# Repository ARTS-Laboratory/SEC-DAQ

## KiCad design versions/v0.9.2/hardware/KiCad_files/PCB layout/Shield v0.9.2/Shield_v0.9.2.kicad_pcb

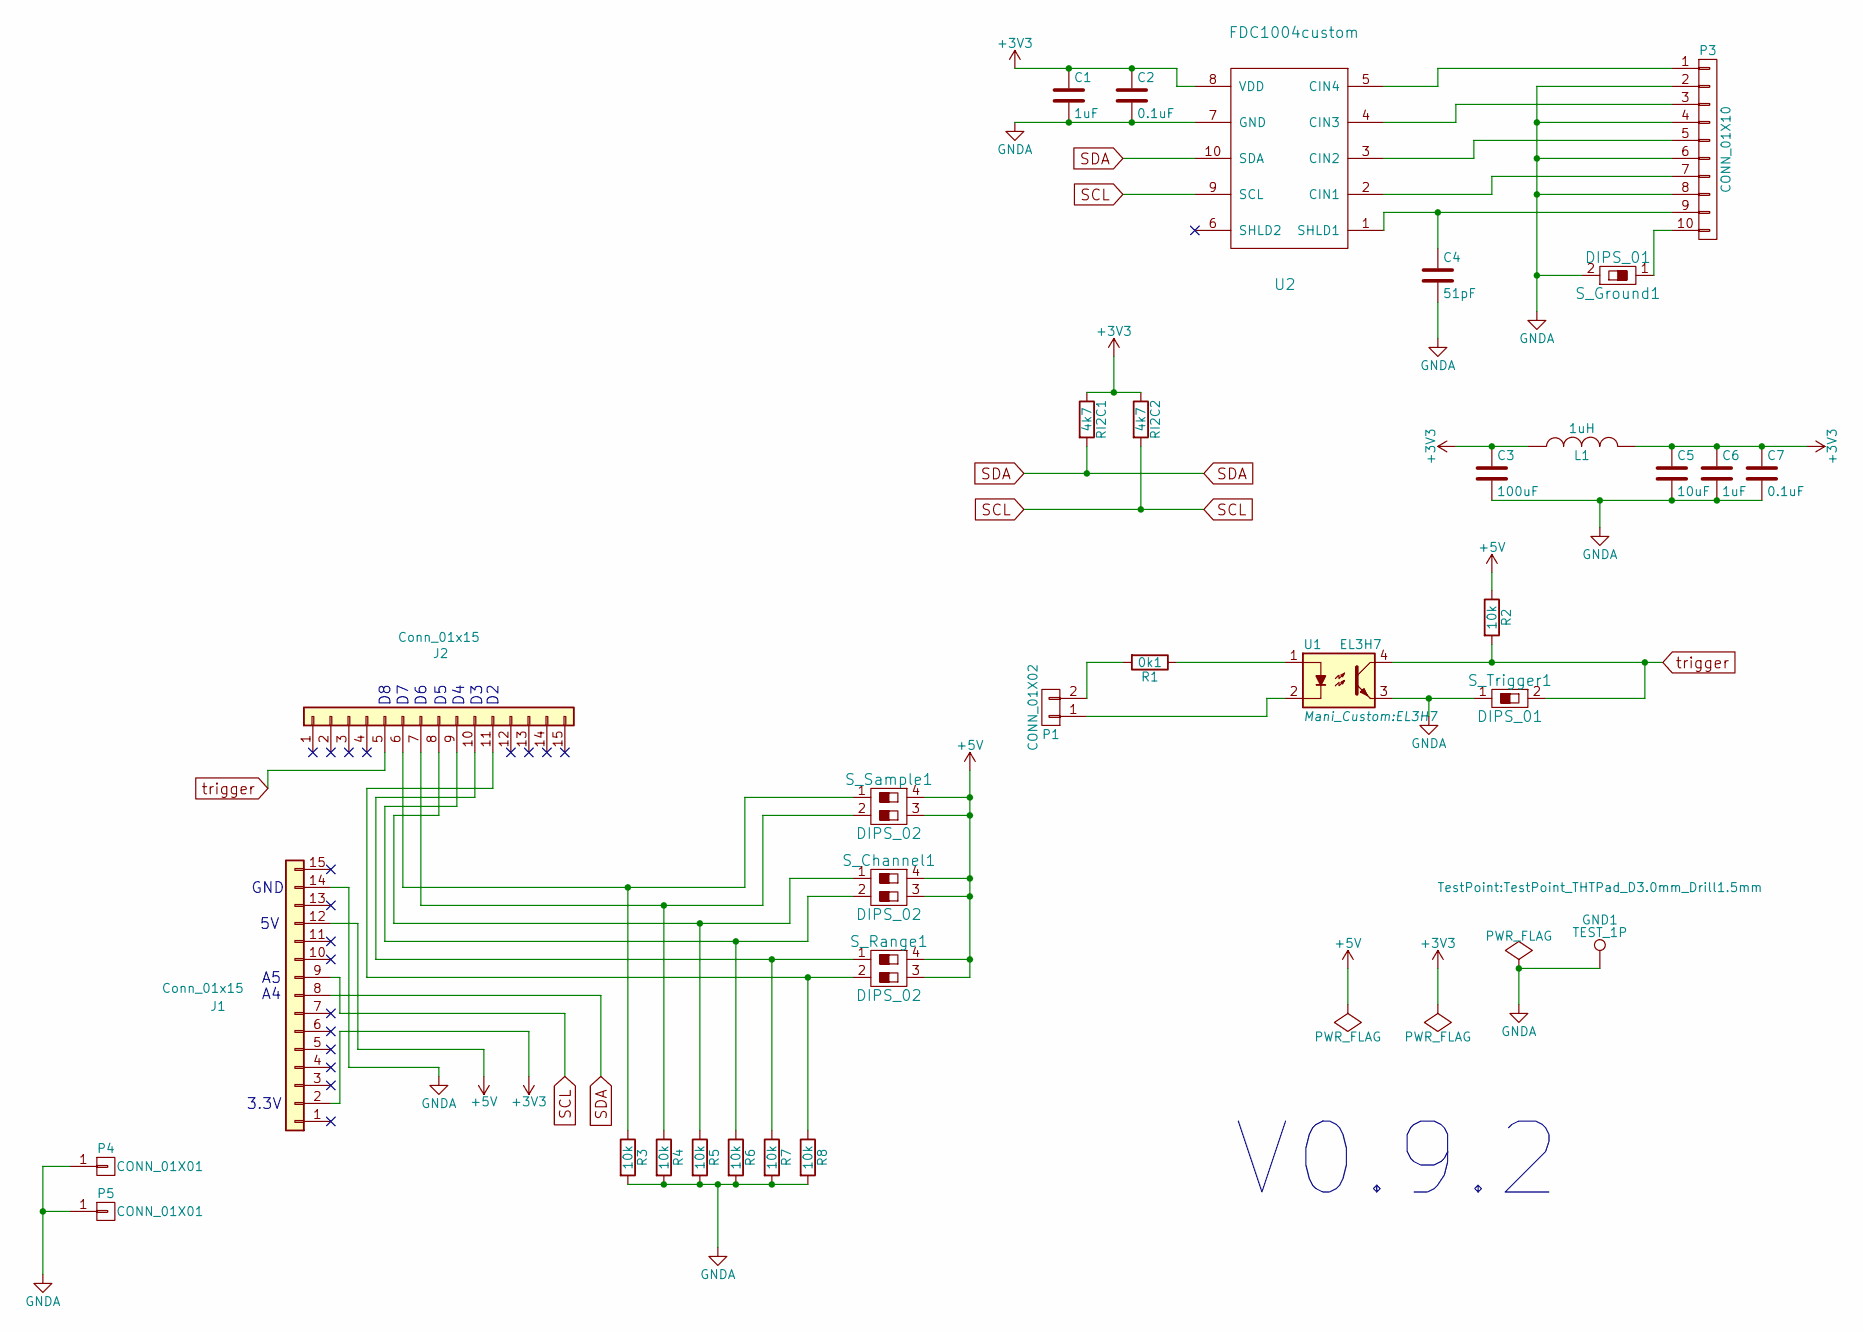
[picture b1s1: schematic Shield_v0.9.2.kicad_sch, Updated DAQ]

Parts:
C1, C6: 1uF; C_0805_2012Metric_Pad1.18x1.45mm_HandSolder
C2, C7: 0.1uF; C_0805_2012Metric_Pad1.18x1.45mm_HandSolder
C3: 100uF; C_1206_3216Metric_Pad1.33x1.80mm_HandSolder
C4: 51pF; C_0805_2012Metric_Pad1.18x1.45mm_HandSolder
C5: 10uF; C_0805_2012Metric_Pad1.18x1.45mm_HandSolder
GND1: TEST_1P; TestPoint_THTPad_D3.0mm_Drill1.5mm
J1, J2: Conn_01x15; PinSocket_1x15_P2.54mm_Vertical
L1: 1uH; R_0805_2012Metric_Pad1.20x1.40mm_HandSolder
P1: CONN_01X02; PinHeader_1x02_P2.54mm_Vertical
P3: CONN_01X10; DSUB-9_surface_mount
P4, P5: CONN_01X01; GNDA_Pad_4.064mm
R1: 0k1; R_1206_3216Metric_Pad1.30x1.75mm_HandSolder
R2, R3, R4, R5, R6, R7, R8: 10k; R_1206_3216Metric_Pad1.30x1.75mm_HandSolder
RI2C1, RI2C2: 4k7; R_1206_3216Metric_Pad1.30x1.75mm_HandSolder
S_Channel1: DIPS_02; SW_DIP_SPSTx02_Slide_9.78x7.26mm_W7.62mm_P2.54mm
S_Ground1: DIPS_01; SW_DIP_SPSTx01_Slide_9.78x4.72mm_W7.62mm_P2.54mm
S_Range1: DIPS_02; SW_DIP_SPSTx02_Slide_9.78x7.26mm_W7.62mm_P2.54mm
S_Sample1: DIPS_02; SW_DIP_SPSTx02_Slide_9.78x7.26mm_W7.62mm_P2.54mm
S_Trigger1: DIPS_01; SW_DIP_SPSTx01_Slide_9.78x4.72mm_W7.62mm_P2.54mm
U1: EL3H7
U2: FDC1004custom; SOIC_10_FDC1004

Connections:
+3V3: C1.1, C2.1, C3.1, C5.1, C6.1, C7.1, J1.2, L1.1, L1.2, RI2C1.1, RI2C2.1, U2.8 (VDD)
+5V: J1.12, R2.1, S_Channel1.3, S_Channel1.4, S_Range1.3, S_Range1.4, S_Sample1.3, S_Sample1.4
GNDA: C1.2, C2.2, C3.2, C4.2, C5.2, C6.2, C7.2, GND1.1 (1_1), J1.14, P3.2, P3.4, P3.6, P3.8, P4.1 (P1_1), P5.1 (P1_1), R3.2, R4.2, R5.2, R6.2, R7.2, R8.2, S_Ground1.2, S_Trigger1.1, U1.3, U2.7 (GND)
unnamed: J2.6, R3.1, S_Sample1.1
unnamed: J2.7, R4.1, S_Sample1.2
unnamed: J2.8, R5.1, S_Channel1.1
unnamed: J2.9, R6.1, S_Channel1.2
unnamed: J2.10, R7.1, S_Range1.1
unnamed: J2.11, R8.1, S_Range1.2
unnamed: P1.1, U1.2
unnamed: P1.2, R1.2
unnamed: P3.1, U2.5 (CIN4)
unnamed: P3.3, U2.4 (CIN3)
unnamed: P3.5, U2.3 (CIN2)
unnamed: P3.7, U2.2 (CIN1)
unnamed: C4.1, P3.9, U2.1 (SHLD1)
unnamed: P3.10, S_Ground1.1
unnamed: R1.1, U1.1
SCL: J1.9, RI2C2.2, U2.9 (SCL)
SDA: J1.8, RI2C1.2, U2.10 (SDA)
trigger: J2.5, R2.2, S_Trigger1.2, U1.4

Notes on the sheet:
3.3V
V0.9.2
GND

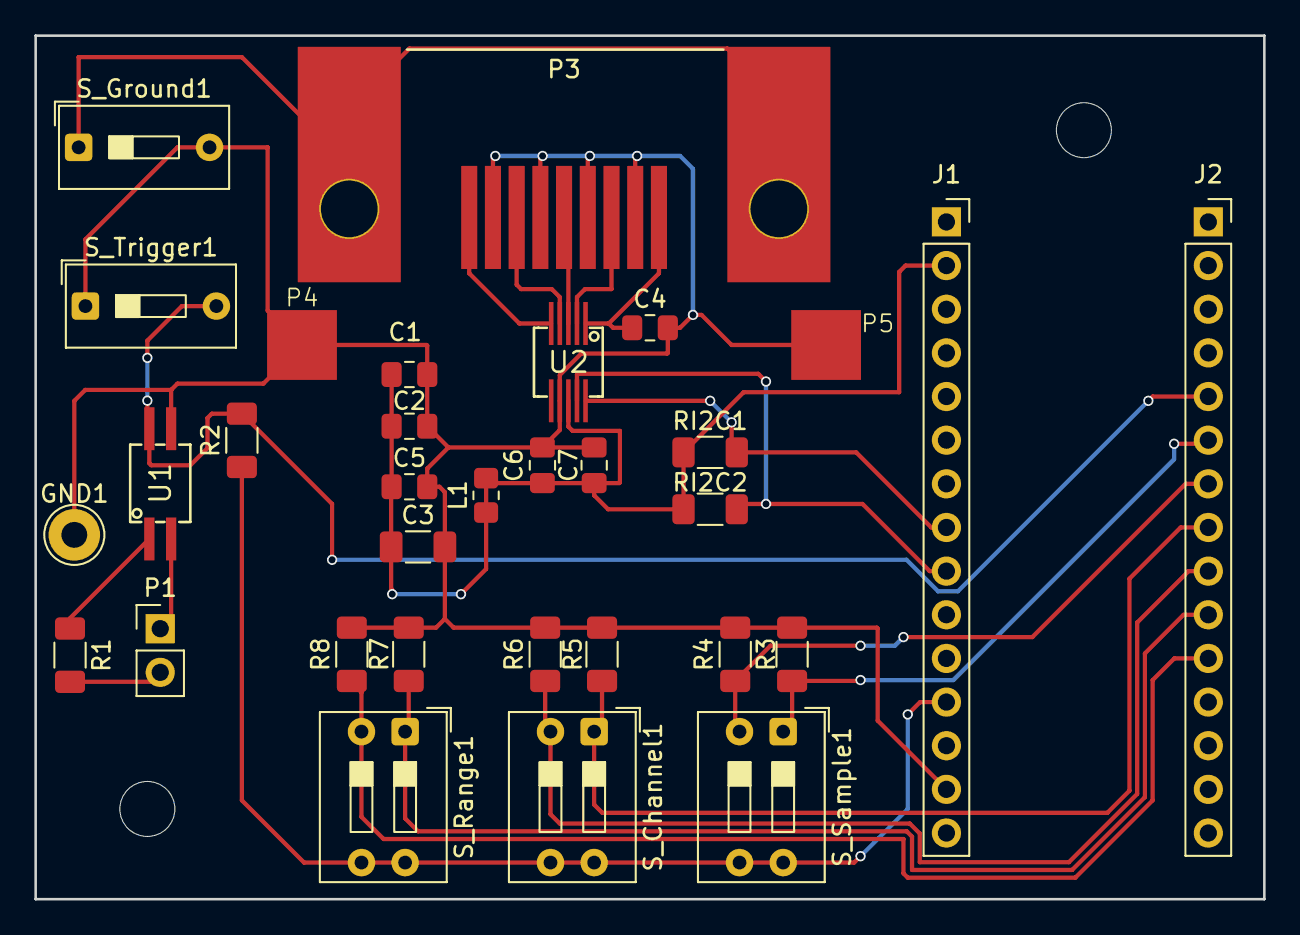
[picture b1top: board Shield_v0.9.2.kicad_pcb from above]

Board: 2 copper layers, 71.5 x 50.2 mm, 32 parts (0 on the bottom side), 21 nets.
